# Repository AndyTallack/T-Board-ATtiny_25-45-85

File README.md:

T-Board-Atiny 25/45/85
======================

T-Board for use on Breadboard - Attiny 25/45/85

This is a series of boards to speed up development of your own standalone ATMega/ATTiny projects.  The T-Board houses the microprocessor, power-supply and FTDI interface, with a breadboard-compatible footprint.  This allows you to get up and running fast with the core ATMega/ATTiny "heart" of your project.

This board is based on the great Arduino concept, and is compatible with the Arduino IDE.  It differs in that it:
- allows you to switch between 3.3V and 5V
- allows you to select crystals for low-power applications
- fits snugly into a breadboard, keeping your project together

There are 2 sets of schematic:
- T-Board-45-85 Etch:	1-layer, for hand-etching.  No ICSP header
- T-Board-45-85 PCB:	2-layer, for production-house.  With ICSP header

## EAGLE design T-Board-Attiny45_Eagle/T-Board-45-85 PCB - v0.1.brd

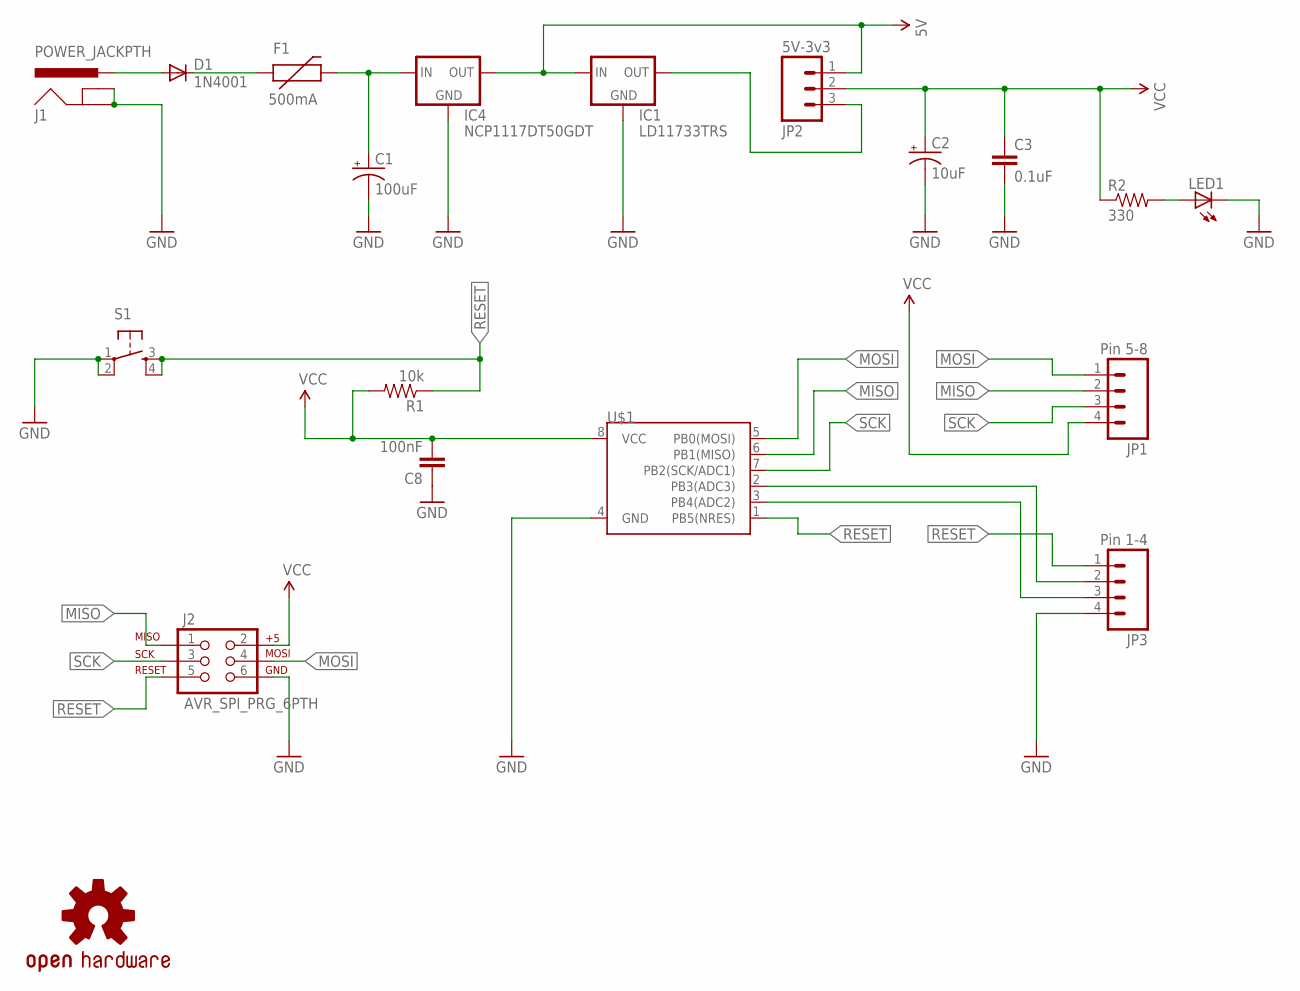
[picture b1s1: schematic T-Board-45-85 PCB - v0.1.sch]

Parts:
C1: 100uF; CPOL-RADIAL-100UF-25V
C2: 10uF; CPOL-RADIAL-10UF-25V
C3: 0.1uF; 1206
C8: 100nF; 1206
D1: 1N4001; DIODE-1N4001
F1: 500mA; PTC
IC1: LD11733TRS; SOT223
IC4: NCP1117DT50GDT; DPACK
J1: POWER_JACKPTH; POWER_JACK_PTH
J2: AVR_SPI_PRG_6PTH; 2X3
JP1: Pin 5-8; 1X04
JP2: 5V-3v3; 1X03
JP3: Pin 1-4; 1X04
LED1: LED1206; LED-1206
LOGO1: OSHW-LOGOS; OSHW-LOGO-S
R1: 10k; 1206
R2: 330; 1206
S1: TAC_SWITCHPTH; TACTILE-PTH
U$1: ATTINY45TINY45-20-DIP; DIP08

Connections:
5V: IC1.3 (IN), IC4.4 (OUT), JP2.1
GND: C1.2 (-), C2.2 (-), C3.2, C8.1, IC1.1 (GND), IC4.1 (GND), J1.GND, J1.GNDBREAK, J2.6, JP3.4, LED1.C, S1.1, S1.2, U$1.4 (GND)
MISO: J2.1, JP1.2, U$1.6 (PB1(MISO))
MOSI: J2.4, JP1.1, U$1.5 (PB0(MOSI))
unnamed: D1.A, J1.PWR
unnamed: D1.C, F1.P$1 (1)
unnamed: C1.1 (+), F1.P$2 (2), IC4.3 (IN)
unnamed: JP3.2, U$1.2 (PB3(ADC3))
unnamed: JP3.3, U$1.3 (PB4(ADC2))
unnamed: LED1.A, R2.2
unnamed: IC1.4 (OUT), JP2.3
RESET: J2.5, JP3.1, R1.1, S1.3, S1.4, U$1.1 (PB5(NRES))
SCK: J2.3, JP1.3, U$1.7 (PB2(SCK/ADC1))
VCC: C2.1 (+), C3.1, C8.2, J2.2, JP1.4, JP2.2, R1.2, R2.1, U$1.8 (VCC)

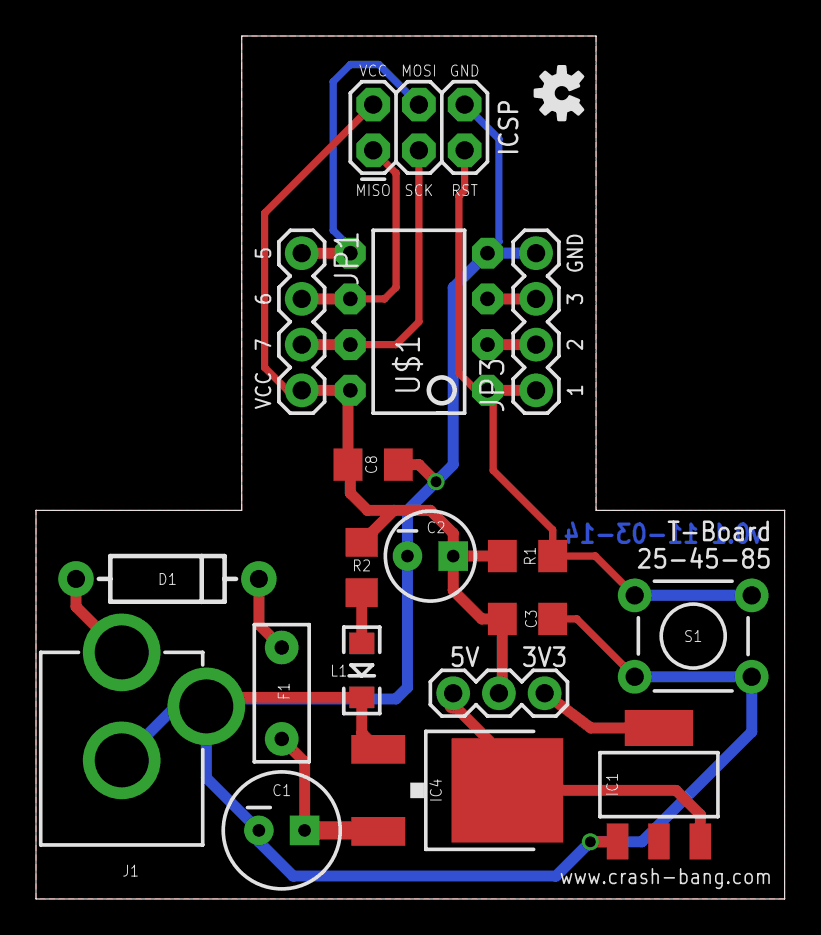
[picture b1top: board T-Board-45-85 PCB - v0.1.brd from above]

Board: 2 copper layers, 41.6 x 47.9 mm, 19 parts (0 on the bottom side), 14 nets.

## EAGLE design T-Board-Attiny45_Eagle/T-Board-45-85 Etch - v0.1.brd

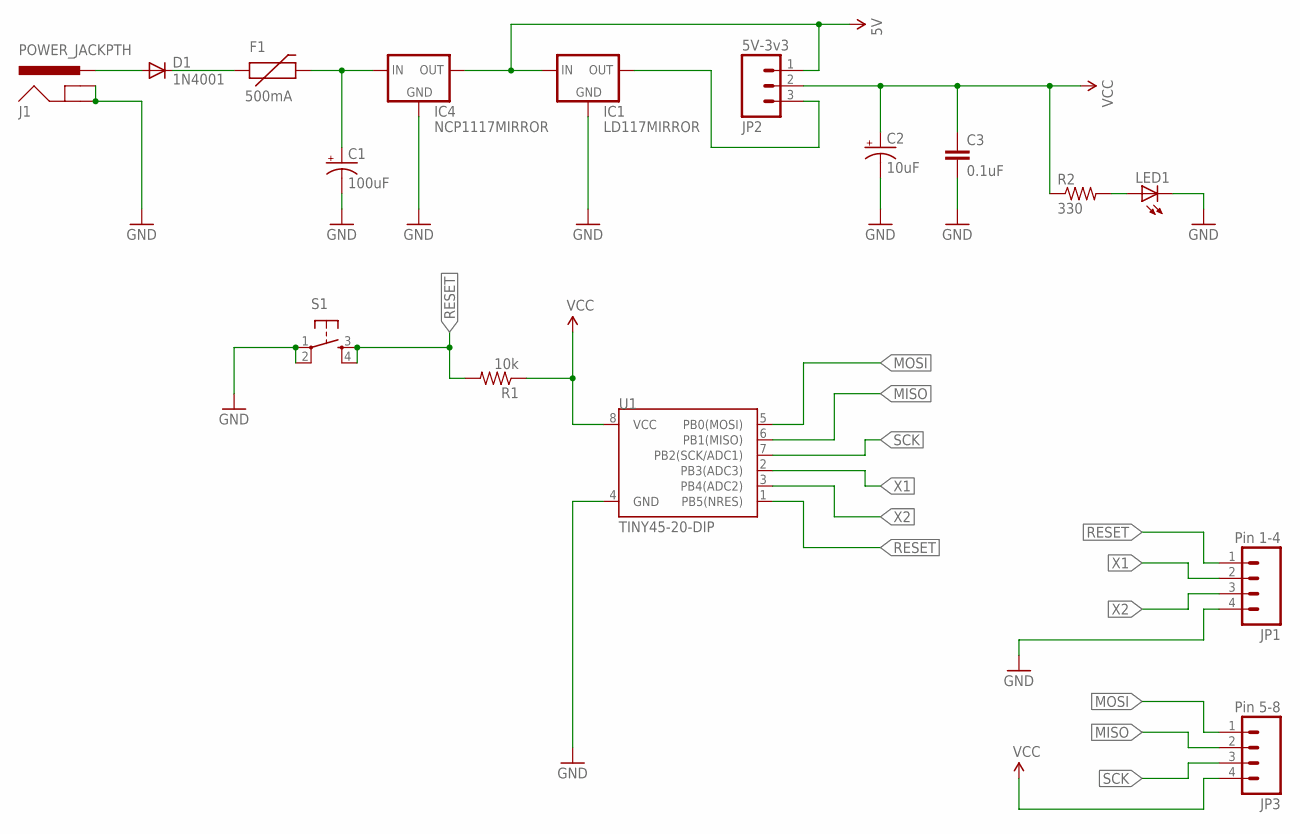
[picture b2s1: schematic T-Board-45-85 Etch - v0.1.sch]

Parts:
C1: 100uF; CPOL-RADIAL-100UF-25V
C2: 10uF; CPOL-RADIAL-10UF-25V
C3: 0.1uF; 1206
D1: 1N4001; DIODE-1N4001
F1: 500mA; PTC
IC1: LD117MIRROR; SOT223
IC4: NCP1117MIRROR; DPACK
J1: POWER_JACKPTH; POWER_JACK_PTH
JP1: Pin 1-4; 1X04
JP2: 5V-3v3; 1X03
JP3: Pin 5-8; 1X04
LED1: LED1206; LED-1206
R1: 10k; 1206
R2: 330; 1206
S1: TAC_SWITCHPTH; TACTILE-PTH
U1: TINY45-20-DIP; DIP08

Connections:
5V: IC1.1 (IN), IC4.4 (OUT), JP2.1
GND: C1.2 (-), C2.2 (-), C3.2, IC1.3 (GND), IC4.3 (GND), J1.GND, J1.GNDBREAK, JP1.4, LED1.C, S1.1, S1.2, U1.4 (GND)
MISO: JP3.2, U1.6 (PB1(MISO))
MOSI: JP3.1, U1.5 (PB0(MOSI))
unnamed: D1.A, J1.PWR
unnamed: D1.C, F1.P$1 (1)
unnamed: C1.1 (+), F1.P$2 (2), IC4.1 (IN)
unnamed: LED1.A, R2.2
unnamed: IC1.4 (OUT), JP2.3
RESET: JP1.1, R1.2, S1.3, S1.4, U1.1 (PB5(NRES))
SCK: JP3.3, U1.7 (PB2(SCK/ADC1))
VCC: C2.1 (+), C3.1, JP2.2, JP3.4, R1.1, R2.1, U1.8 (VCC)
X1: JP1.2, U1.2 (PB3(ADC3))
X2: JP1.3, U1.3 (PB4(ADC2))

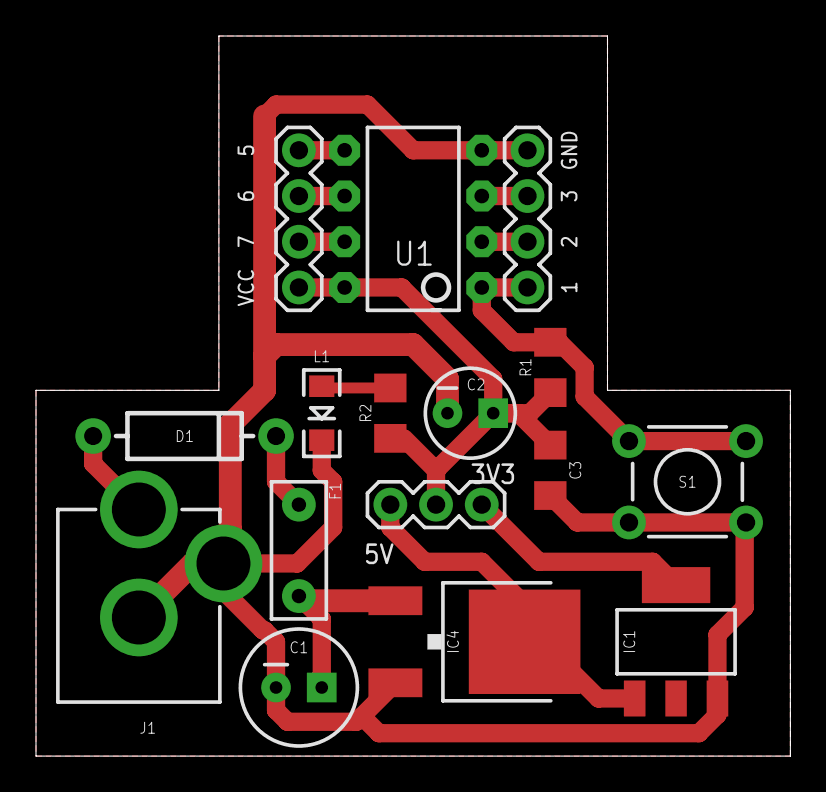
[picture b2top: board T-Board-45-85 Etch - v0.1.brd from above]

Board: 2 copper layers, 41.9 x 40.0 mm, 16 parts (0 on the bottom side), 14 nets.

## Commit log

2014-02-14 v0.1 - Initial Prototype
    Untested prototype
2014-03-16 v0.2 - 2-sided prototype
    2-sided prototype send to OSHPark to fab. Includes:
    - ICSP header
    - Consistency in trace width
2014-04-11 Adjusted header pins
    Header pins spacing corrected to fit breadboard more precisely

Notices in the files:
parts and their libraries:
SparkFun-Connectors: Licensing: CC v3.0 Share-Alike You are welcome to use this library for commercial purposes.
